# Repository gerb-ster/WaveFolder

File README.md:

# WaveFolder

This effect module is based on a design/schematic I found on YouTube, by a guy named Adamski. It’s a nice module to generate some interesting sound effects.

## Status: Finished

- done: first schematic & board design
- done: breadboard and test
- done: design frontpanel
- done: order PCB and build prototype

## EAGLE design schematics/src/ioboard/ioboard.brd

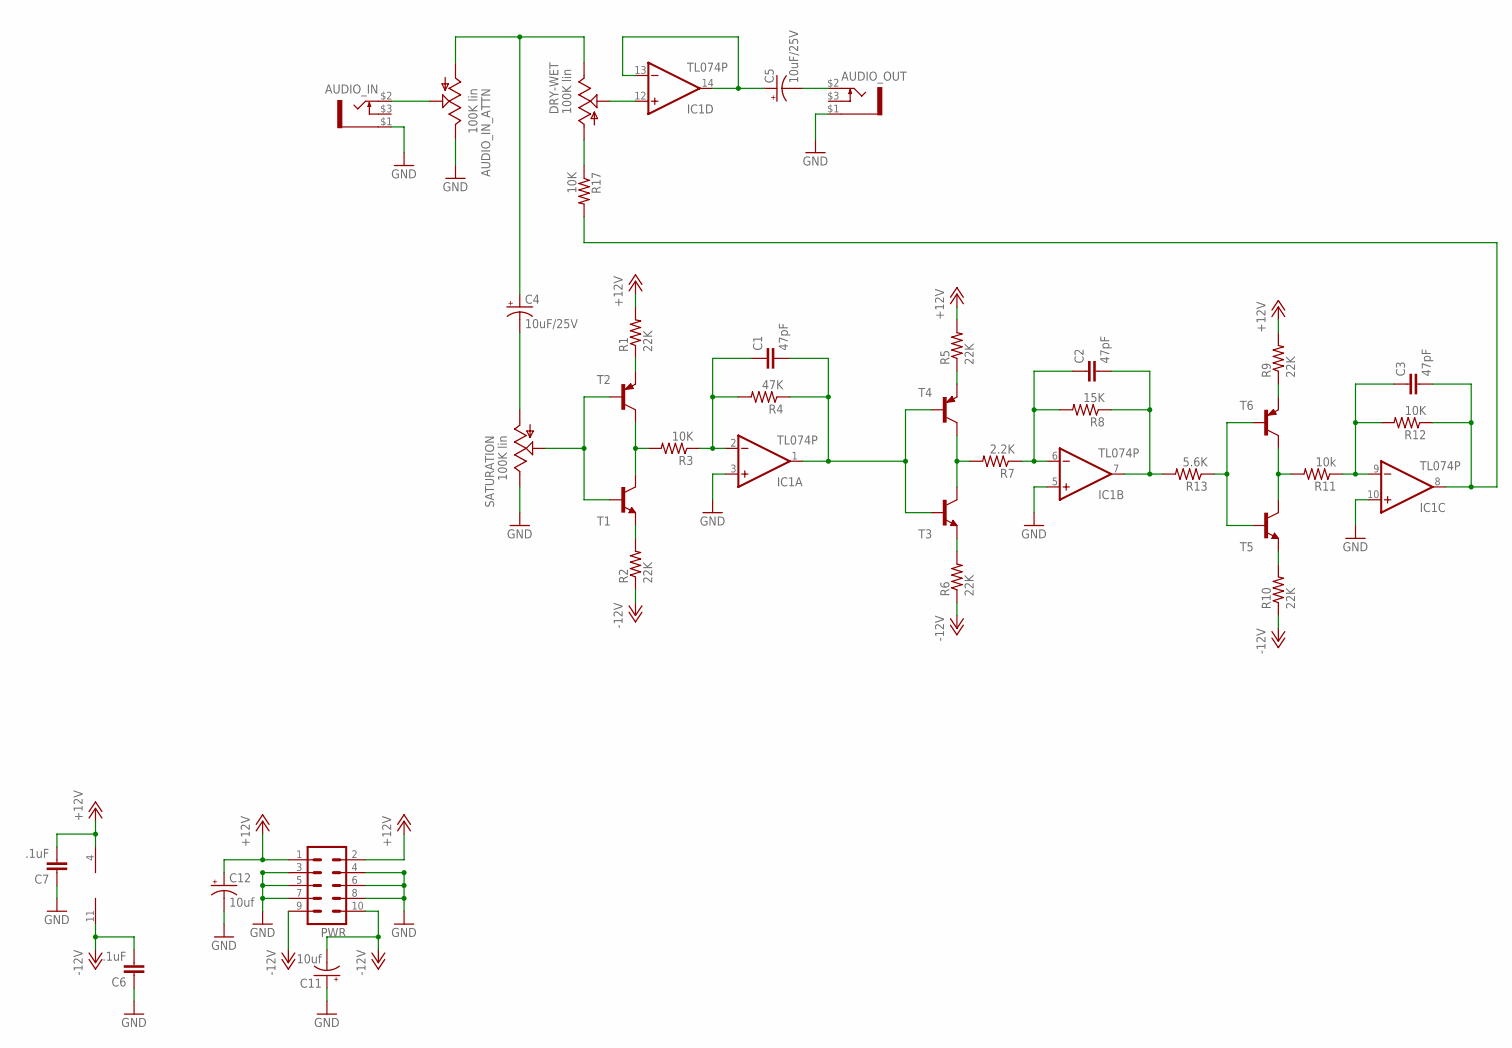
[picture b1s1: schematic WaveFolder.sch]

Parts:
AUDIO_IN: PJ-323PJ-323; PJ-323
AUDIO_IN_ATTN: 100K lin; EVUF
AUDIO_OUT: PJ-323PJ-323; PJ-323
C1, C2, C3: 47pF; C025-024X044
C4, C5: 10uF/25V; E2,5-6
C6, C7: .1uF; C025-024X044
C11, C12: 10uf; E2,5-5
DRY-WET: 100K lin; EVUF
IC1: TL074P; DIL14
PWR: ML10
R1, R2, R5, R6, R9, R10: 22K; 0207/7
R3, R12, R17: 10K; 0207/7
R4: 47K; 0207/7
R7: 2.2K; 0207/7
R8: 15K; 0207/7
R11: 10k; 0207/7
R13: 5.6K; 0207/7
SATURATION: 100K lin; EVUF
T1, T3, T5: 2N3904-NPN-TO92-EBC; TO92-EBC
T2, T4, T6: 2N3906-PNP-TO92-EBC; TO92-EBC

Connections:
+12V: C7.2, C12.+, IC1.4 (V+), PWR.1, PWR.2, R1.2, R5.2, R9.2
-12V: C6.2, C11.-, IC1.11 (V-), PWR.9, PWR.10, R2.1, R6.1, R10.1
GND: AUDIO_IN.$1 (3), AUDIO_IN_ATTN.3 (E), AUDIO_OUT.$1 (3), C6.1, C7.1, C11.+, C12.-, IC1.3 (+IN), IC1.5 (+IN), IC1.10 (+IN), PWR.3, PWR.4, PWR.5, PWR.6, PWR.7, PWR.8, SATURATION.3 (E)
unnamed: R3.2, T1.C, T2.C
unnamed: SATURATION.2 (S), T1.B, T2.B
unnamed: R1.1, T2.E
unnamed: R2.2, T1.E
unnamed: C1.1, IC1.2 (-IN), R3.1, R4.2
unnamed: C1.2, IC1.1 (OUT), R4.1, T3.B, T4.B
unnamed: R7.2, T3.C, T4.C
unnamed: C4.-, SATURATION.1 (A)
unnamed: R5.1, T4.E
unnamed: R6.2, T3.E
unnamed: C2.1, IC1.6 (-IN), R7.1, R8.2
unnamed: C2.2, IC1.7 (OUT), R8.1, R13.2
unnamed: R11.2, T5.C, T6.C
unnamed: R13.1, T5.B, T6.B
unnamed: R9.1, T6.E
unnamed: R10.2, T5.E
unnamed: C3.1, IC1.9 (-IN), R11.1, R12.2
unnamed: C3.2, IC1.8 (OUT), R12.1, R17.2
unnamed: AUDIO_IN.$2 (1), AUDIO_IN_ATTN.2 (S)
unnamed: AUDIO_IN_ATTN.1 (A), C4.+, DRY-WET.3 (E)
unnamed: DRY-WET.1 (A), R17.1
unnamed: DRY-WET.2 (S), IC1.12 (+IN)
unnamed: C5.+, IC1.13 (-IN), IC1.14 (OUT)
unnamed: AUDIO_OUT.$2 (1), C5.-

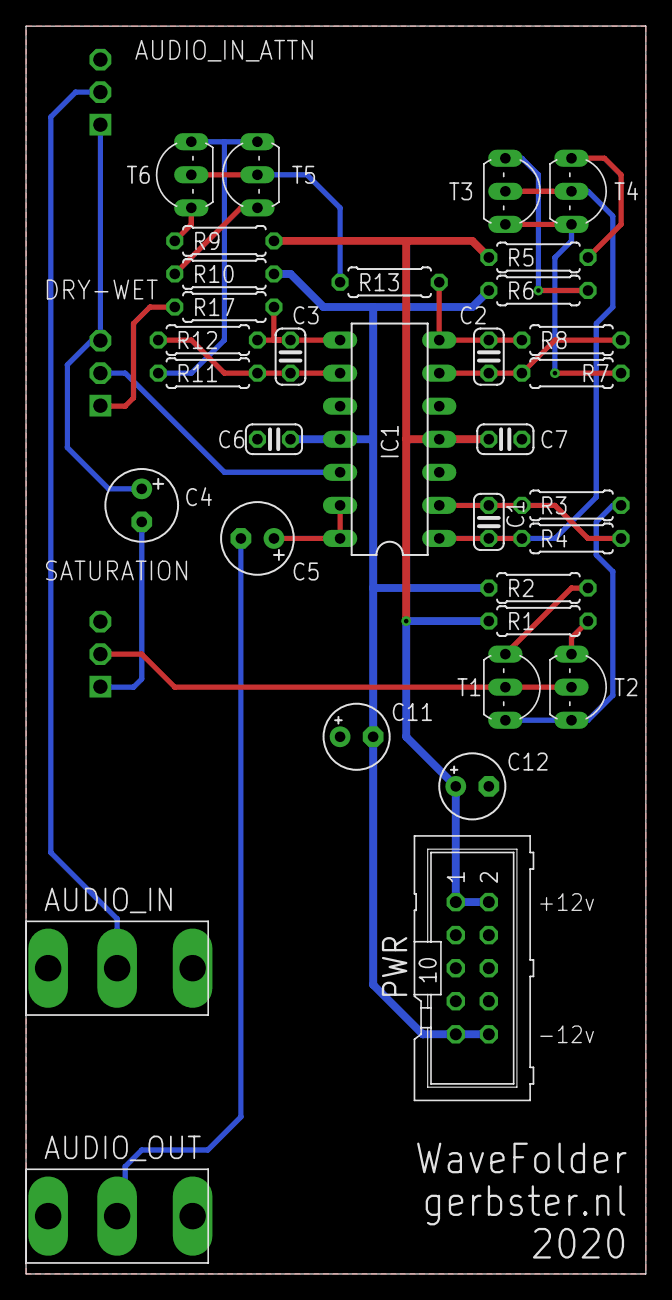
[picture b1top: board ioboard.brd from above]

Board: 2 copper layers, 47.6 x 95.9 mm, 36 parts (0 on the bottom side), 27 nets.

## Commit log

2021-05-06 some files
2021-05-07 Added files & structure
2021-05-10 Added Status
2021-05-11 Added Status & Images
2021-08-06 Updated some schematics and docs
2021-08-10 Fixed some bugs and updated documentation
2022-04-20 Some updates & bugfixes
2022-04-22 Fixed schematics & descriptions
2022-05-17 Updated Firmware
2022-05-18 Updated Faceplates
2022-05-18 Fixed issues
2022-05-21 Fixed schematics
2022-05-28 General updates
